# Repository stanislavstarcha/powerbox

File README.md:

# Install and run firmware

Add paths to your bash/zsh rc for convenience 

```shell
export POWERBOX_HOME=$HOME/powerbox
export LVGL_HOME=$HOME/lvgl_micropython
```

```shell
mkdir $POWERBOX_HOME
cd $POWERBOX_HOME
git clone https://github.com/stanislavstarcha/powerbox .
```

## Install LVGL micropython

```shell
mkdir $LVGL_HOME
cd $LVGL_HOME
git clone https://github.com/lvgl-micropython/lvgl_micropython .
```

### Copy fonts
```shell
cd $POWEBOX_HOME
cp ./resources/fonts/Roboto-Black.ttf $LVGL_HOME/lib/lvgl/scripts/built_in_font
cp ./resources/fonts/Roboto-Regular.ttf $LVGL_HOME/lib/lvgl/scripts/built_in_font
cp ./resources/fonts/Material-Sharp-28.ttf $LVGL_HOME/lib/lvgl/scripts/built_in_font

```

### Build fonts

Modify `$LVGL_HOME/lib/lvgl/scripts/built_in_font/generate_all.py` and add 

```python
print("\nGenerating 12 px Roboto Ukrainian")
os.system("lv_font_conv --no-compress --no-prefilter --bpp 2 --size 12 --font Roboto-Regular.ttf --format lvgl -o lv_font_roboto_12.c -r 0xB0,0x20-0x22,0x25,0x27-0x40,0x5B-0x5F,0x7B-0x7D,0xA0,0xA7,0xA9,0xAB,0xBB,0x2BC,0x404,0x406-0x407,0x410-0x429,0x42C,0x42E-0x449,0x44C,0x44E-0x44F,0x454,0x456-0x457,0x490-0x491,0x2011,0x2013,0x2019,0x201C,0x201E,0x2030,0x20AC,0x2116")

print("\nGenerating 24 px Glyphs")
os.system("lv_font_conv --no-compress --no-prefilter --bpp 2 --size 24 --font Material-Sharp-28.ttf --format lvgl -o lv_font_material_24.c -r 0xEAC3,0xEAC9,0xEAD0,0xEACF,0xE000,0xe1a7,0xe1a8,0xf156,0xE7EE,0xe5d3,0xe322,0xe87d")

print("\nGenerating 24 px Roboto")
os.system("lv_font_conv --no-compress --no-prefilter --bpp 2 --size 26 --font Roboto-Black.ttf --format lvgl -o lv_font_roboto_24.c -r 0x20,0x30-0x39,0x412,0x442")

print("\nGenerating 120 px Roboto")
os.system("lv_font_conv --no-compress --no-prefilter --bpp 2 --size 120 --font Roboto-Black.ttf --format lvgl -o lv_font_roboto_120.c --symbols 0123456789%")
```

and then build the fonts

```shell
cd $LVGL_HOME/lib/lvgl/scripts/built_in_font
python generate_all.py
```

### Modify headers

Open `$LVGL_HOME/lib/lvconf.h`

Set to 0 (disable) all `#define LV_FONT_MONTSERRAT_*`
and define custom fonts built earlier.

```
#define LV_FONT_MONTSERRAT_14 0
...

#define LV_FONT_CUSTOM_DECLARE LV_FONT_DECLARE(lv_font_roboto_12) LV_FONT_DECLARE(lv_font_roboto_24) LV_FONT_DECLARE(lv_font_roboto_120) LV_FONT_DECLARE(lv_font_material_24)

#define LV_FONT_DEFAULT &lv_font_roboto_12
```

## Build firmware

```shell
cd $LVGL_HOME
python make.py esp32 BOARD=ESP32_GENERIC_S3 DISPLAY=ILI9488 \
FROZEN_MANIFEST=$POWERBOX_HOME/manifest.py BOARD_VARIANT=SPIRAM_OCT \
--flash-size=16 \ 
--ota
```

### Flash firmware

Connect ESP32-S3 to USB and find the port `ls /dev/tty*`

A typical serial port should look like this 
- `/dev/tty.usbmodem11101`
- `/dev/cu.usbserial-0001`
- `/dev/tty.usbmodem1234561`

Note: On MacOS you may need a CH34xVCPDriver that would create a new port like
`/dev/tty.wchusbserial59710258441`

```shell
cd $LVGL_HOME

python -m esptool --chip esp32s3 -p /dev/tty.wchusbserial59710258441 \
-b 460800 --before default_reset --after hard_reset write_flash \
--flash_mode dio --flash_size 16MB --flash_freq 80m --erase-all \
0x0 /Users/stasstarcha/workspace/lvgl_micropython/build/lvgl_micropy_ESP32_GENERIC_S3-SPIRAM_OCT-16.bin
```

### Build release

Specify the version and run the command to produce bin and json files that
should be attached to a release on GitHub.

```shell
cd $POWEBOX_HOME
python scripts/release.py --version=0.10.0 \
--path=$LVGL_HOME/lib/micropython/ports/esp32/build-ESP32_GENERIC_S3-SPIRAM_OCT/micropython.bin \
--output=../build
 ```

## Development mode

During development, it's easier to update files one by one.

```shell
python initialize.py \
--baud_rate 115200 \
--port /dev/cu.usbserial-0001
```

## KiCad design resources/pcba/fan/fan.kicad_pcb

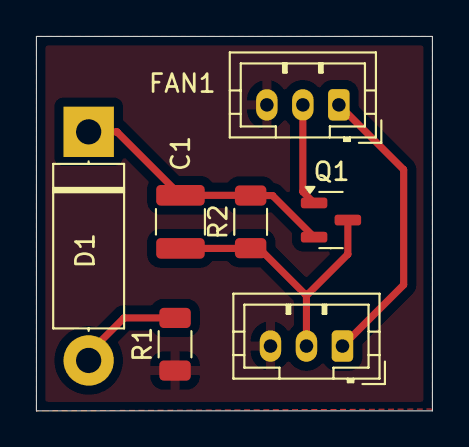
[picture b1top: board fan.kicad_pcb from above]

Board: 2 copper layers, 22.0 x 20.8 mm, 7 parts (0 on the bottom side), 6 nets.

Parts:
C1: 10u; C_1210_3225Metric
D1: D_Zener; D_5W_P12.70mm_Horizontal
FAN1: Conn_01x03_Socket; JST_PH_B3B-PH-K_1x03_P2.00mm_Vertical
INV1: Conn_01x03_Socket; JST_PH_B3B-PH-K_1x03_P2.00mm_Vertical
Q1: PMOS; SOT-23
R1: 1k; R_1206_3216Metric
R2: 10k; R_1206_3216Metric

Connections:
/FAN: FAN1.2 (+), Q1.1 (D)
/TACHOMETER: FAN1.1 (TACH), INV1.1 (TACH)
GND: FAN1.3 (GND), INV1.3 (GND), R1.1
unnamed: D1.2 (A), R1.2
unnamed: C1.1, D1.1 (K), Q1.2 (G), R2.2
unnamed: C1.2, INV1.2 (+), Q1.3 (S), R2.1

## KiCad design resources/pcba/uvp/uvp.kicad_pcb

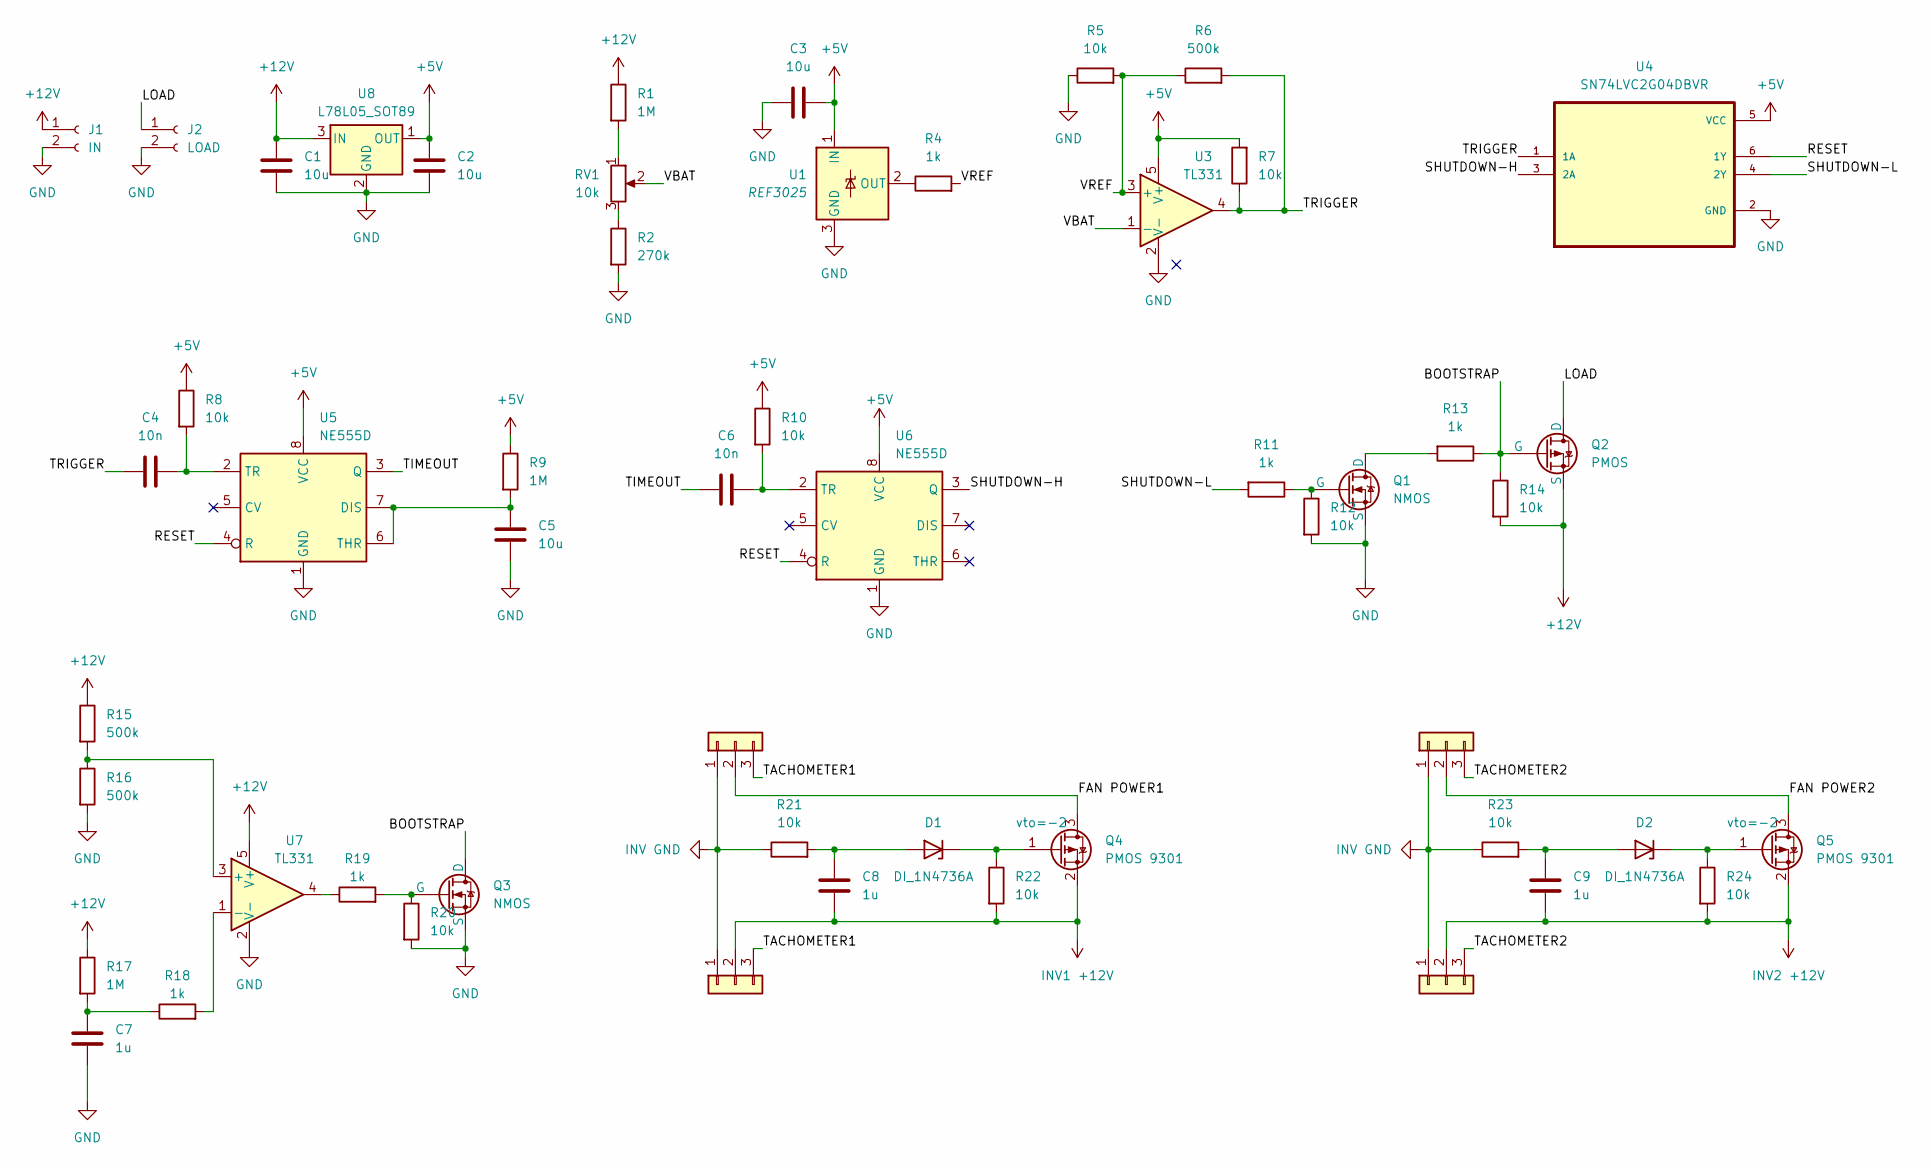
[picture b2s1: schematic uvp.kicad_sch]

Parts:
C1, C2, C3: 10u; C_0805_2012Metric_Pad1.18x1.45mm_HandSolder
C4, C6: 10n; C_0805_2012Metric_Pad1.18x1.45mm_HandSolder
C5: 10u; C_1210_3225Metric_Pad1.33x2.70mm_HandSolder
C7: 1u; C_0805_2012Metric_Pad1.18x1.45mm_HandSolder
C8, C9: 1u; C_1210_3225Metric
D1, D2: D_Zener; D_5W_P12.70mm_Horizontal
IN1: FAN1; JST_PH_S3B-PH-K_1x03_P2.00mm_Horizontal
IN2: INV FAN1; JST_PH_S3B-PH-K_1x03_P2.00mm_Horizontal
IN3: FAN2; JST_PH_S3B-PH-K_1x03_P2.00mm_Horizontal
IN4: INV FAN2; JST_PH_S3B-PH-K_1x03_P2.00mm_Horizontal
J1: IN; JST_XH_S2B-XH-A_1x02_P2.50mm_Horizontal
J2: LOAD; JST_XH_S2B-XH-A_1x02_P2.50mm_Horizontal
Q1, Q3: NMOS; SOT-23
Q2: PMOS; TO-252-2
Q4, Q5: PMOS 9301; SOT-23
R1, R9, R17: 1M; R_0805_2012Metric_Pad1.20x1.40mm_HandSolder
R2: 270k; R_0805_2012Metric_Pad1.20x1.40mm_HandSolder
R4, R11, R13, R18, R19: 1k; R_0805_2012Metric_Pad1.20x1.40mm_HandSolder
R5, R7, R8, R10, R12, R14, R20: 10k; R_0805_2012Metric_Pad1.20x1.40mm_HandSolder
R6, R15, R16: 500k; R_0805_2012Metric_Pad1.20x1.40mm_HandSolder
R21, R22, R23, R24: 10k; R_1206_3216Metric
RV1: 10k; Potentiometer_Runtron_RM-063_Horizontal
U1: REF3025; SOT-23
U3, U7: TL331; SOT-23-5
U4: SN74LVC2G04DBVR; SOT95P280X145-6N
U5, U6: NE555D; SOIC-8_3.9x4.9mm_P1.27mm
U8: L78L05_SOT89; SOT-89-3

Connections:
+5V: C2.2, C3.1, R7.2, R8.1, R9.1, R10.1, U1.1 (IN), U3.5 (V+), U4.5 (VCC), U5.8 (VCC), U6.8 (VCC), U8.1 (OUT)
+12V: C1.2, J1.1, Q2.3 (S), R1.1, R14.2, R15.1, R17.1, U7.5 (V+), U8.3 (IN)
/BOOTSTRAP: Q2.2 (G), Q3.1 (D), R13.1, R14.1
/FAN POWER1: IN1.2, Q4.3 (D)
/FAN POWER2: IN3.2, Q5.3 (D)
/LOAD: J2.1, Q2.1 (D)
/RESET: U4.6 (1Y), U5.4 (R), U6.4 (R)
/SHUTDOWN-H: U4.3 (2A), U6.3 (Q)
/SHUTDOWN-L: R11.2, U4.4 (2Y)
/TACHOMETER1: IN1.3, IN2.3
/TACHOMETER2: IN3.3, IN4.3
/TIMEOUT: C6.1, U5.3 (Q)
/TRIGGER: C4.1, R6.2, R7.1, U3.4, U4.1 (1A)
/VBAT: RV1.2, U3.1 (-)
/VREF: R4.2, R5.2, R6.1, U3.3 (+)
GND: C1.1, C2.1, C3.2, C5.1, C7.2, J1.2, J2.2, Q1.3 (S), Q3.3 (S), R2.2, R5.1, R12.2, R16.2, R20.2, U1.3 (GND), U3.2 (V-), U4.2 (GND), U5.1 (GND), U6.1 (GND), U7.2 (V-), U8.2 (GND)
INV1 +12V: C8.2, IN2.2, Q4.2 (S), R22.2
INV2 +12V: C9.2, IN4.2, Q5.2 (S), R24.2
INV GND: IN1.1, IN2.1, IN3.1, IN4.1, R21.1, R23.1
unnamed: C7.1, R17.2, R18.1
unnamed: C8.1, D1.2 (A), R21.2
unnamed: D1.1 (K), Q4.1 (G), R22.1
unnamed: C9.1, D2.2 (A), R23.2
unnamed: D2.1 (K), Q5.1 (G), R24.1
unnamed: Q1.1 (D), R13.2
unnamed: Q1.2 (G), R11.1, R12.1
unnamed: Q3.2 (G), R19.2, R20.1
unnamed: R1.2, RV1.1
unnamed: R2.1, RV1.3
unnamed: R19.1, U7.4
unnamed: R4.1, U1.2 (OUT)
unnamed: C5.2, R9.2, U5.6 (THR), U5.7 (DIS)
unnamed: C4.2, R8.2, U5.2 (TR)
unnamed: C6.2, R10.2, U6.2 (TR)
unnamed: R15.2, R16.1, U7.3 (+)
unnamed: R18.2, U7.1 (-)

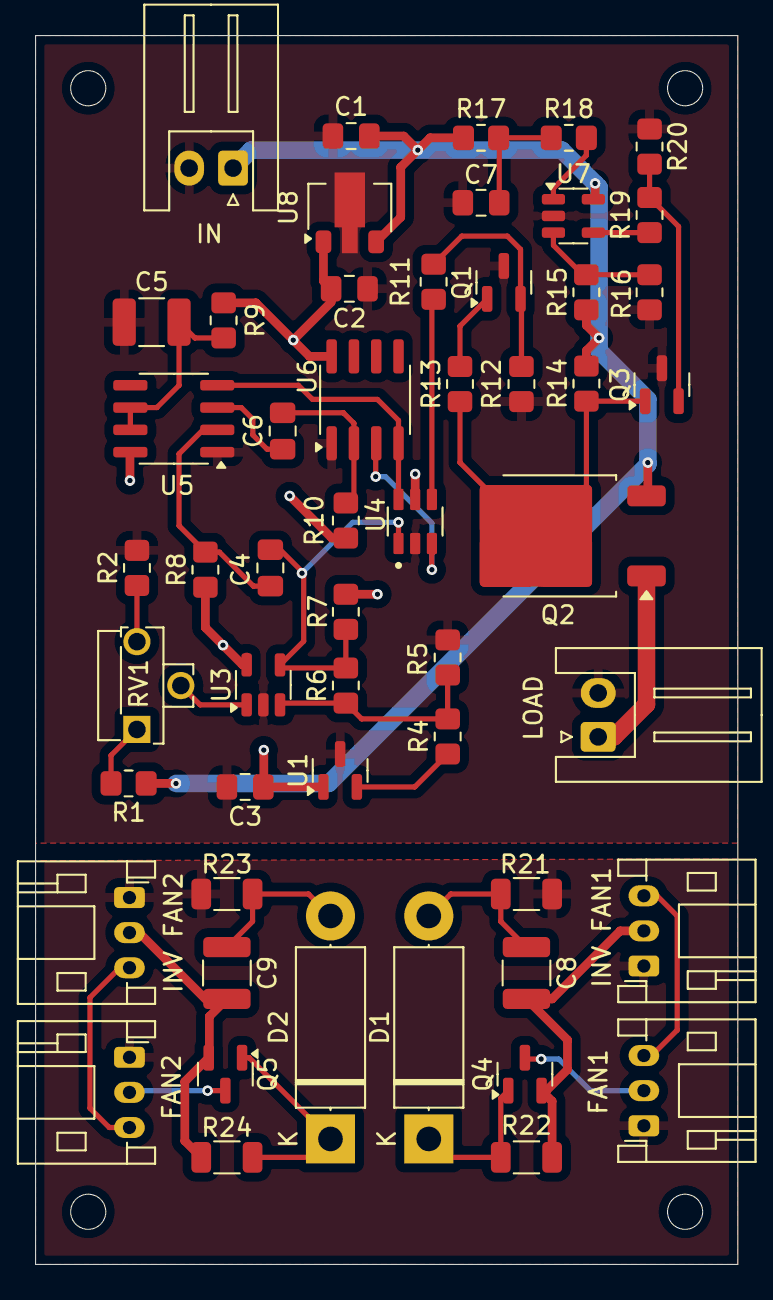
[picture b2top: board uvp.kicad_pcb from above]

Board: 2 copper layers, 40.0 x 70.0 mm, 53 parts (0 on the bottom side), 36 nets.

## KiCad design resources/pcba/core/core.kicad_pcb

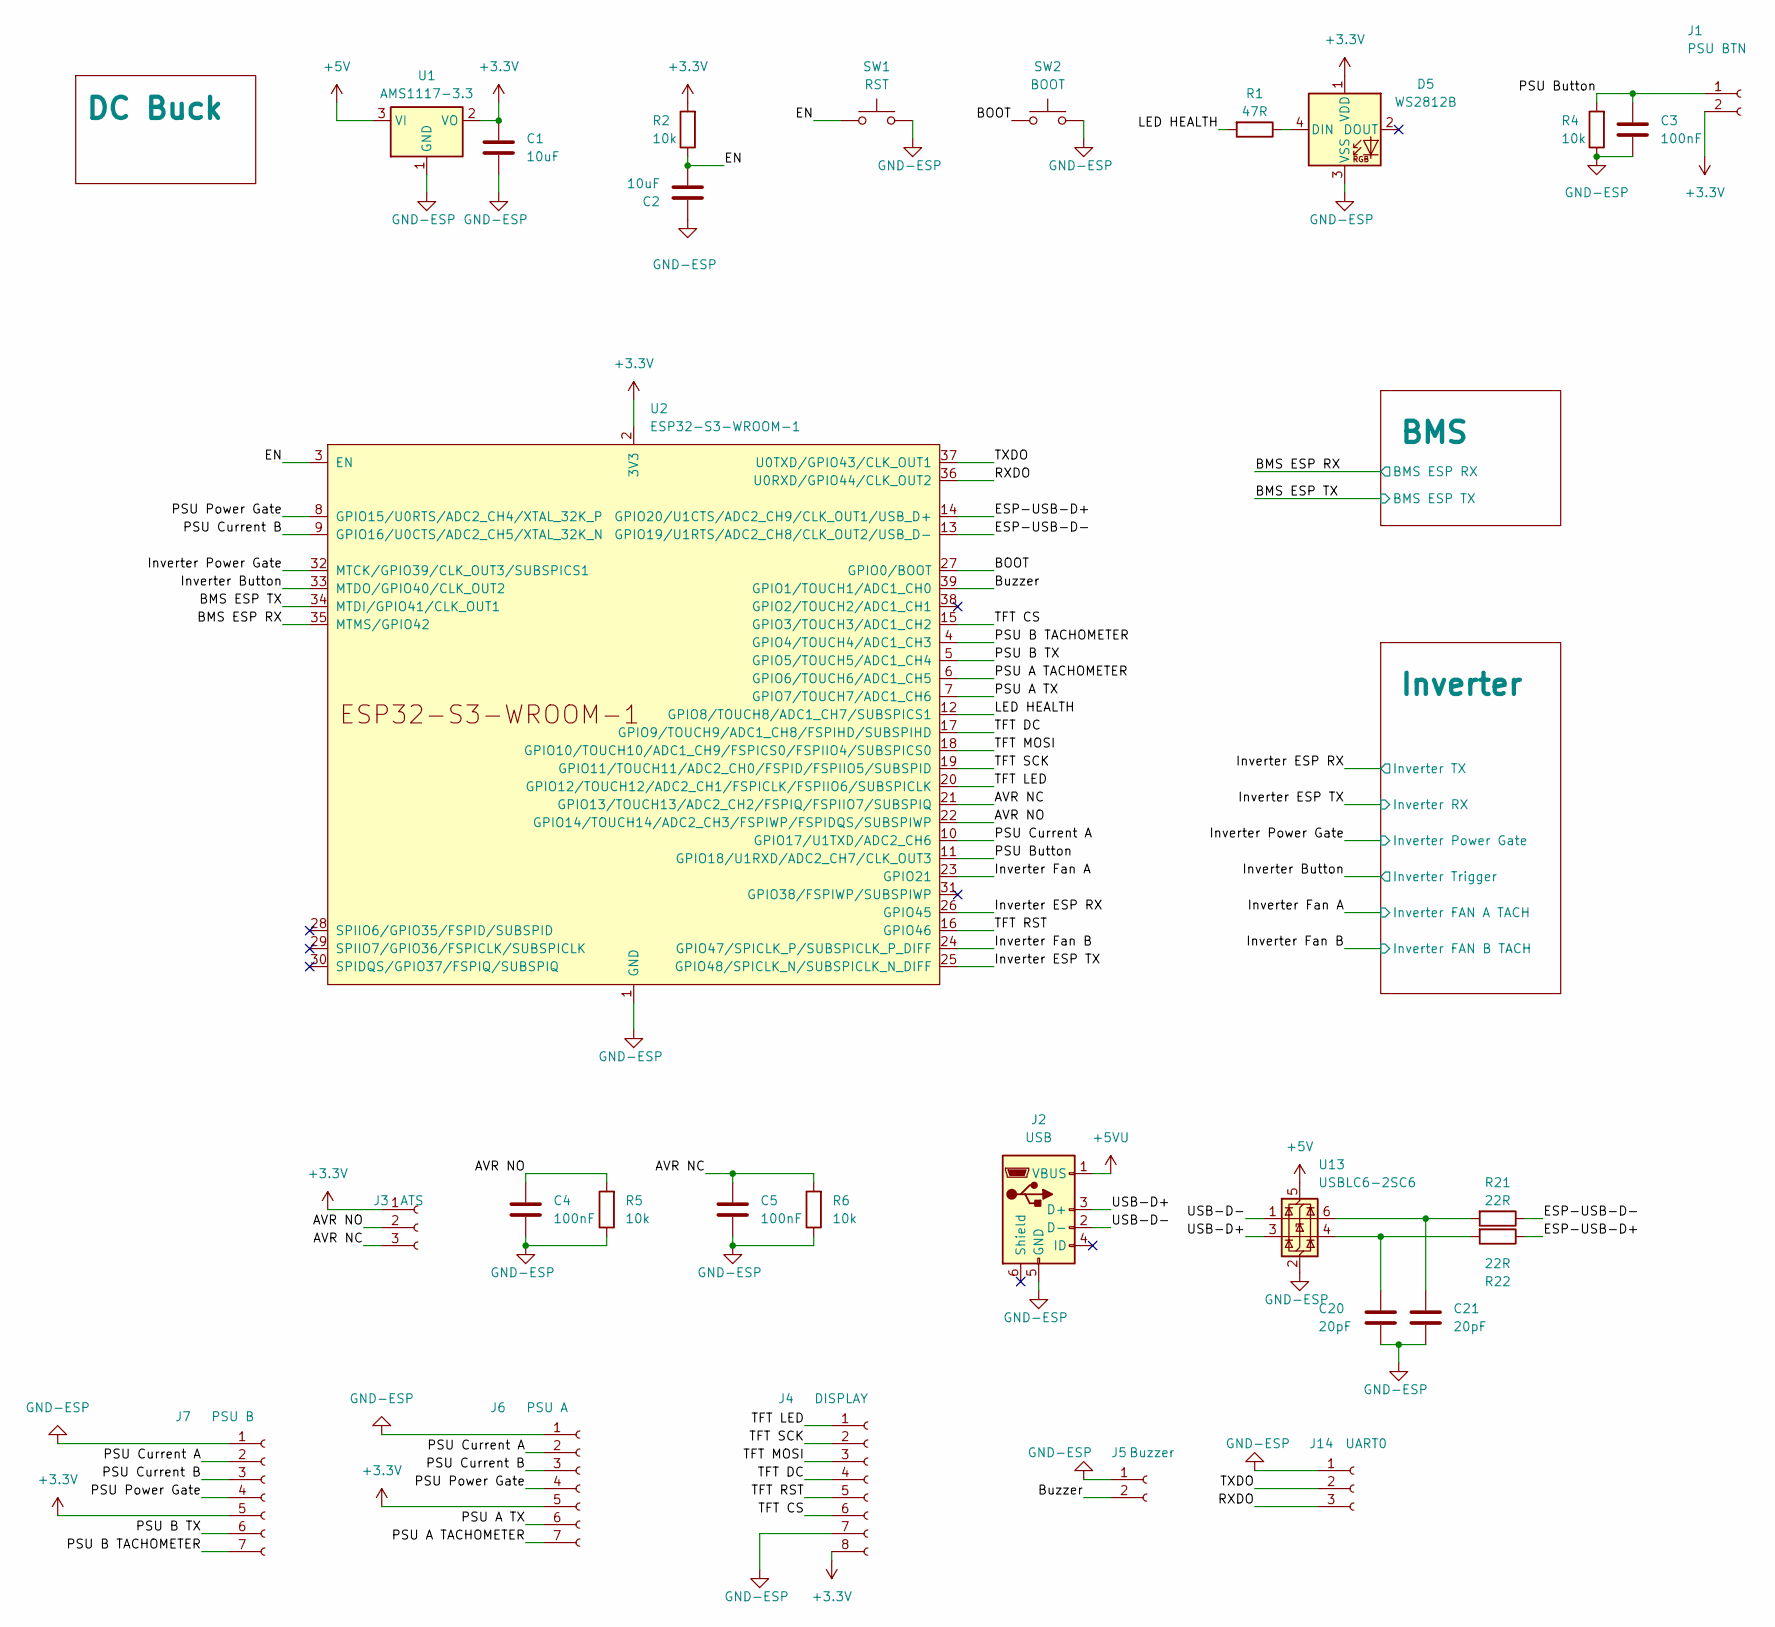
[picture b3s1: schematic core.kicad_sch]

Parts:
C1, C2: 10uF; C_1206_3216Metric
C3, C4, C5: 100nF; C_1206_3216Metric
C20, C21: 20pF; C_0805_2012Metric
D5: WS2812B; LED_WS2812B_PLCC4_5.0x5.0mm_P3.2mm
J1: PSU BTN; JST_PH_B2B-PH-K_1x02_P2.00mm_Vertical
J2: USB; USB_Micro-B_Molex-105017-0001
J3: ATS; JST_PH_B3B-PH-K_1x03_P2.00mm_Vertical
J4: DISPLAY; JST_PH_B8B-PH-K_1x08_P2.00mm_Vertical
J5: Buzzer; JST_PH_B2B-PH-K_1x02_P2.00mm_Vertical
J6: PSU A; JST_PH_B7B-PH-K_1x07_P2.00mm_Vertical
J7: PSU B; JST_PH_B7B-PH-K_1x07_P2.00mm_Vertical
J14: UART0; JST_PH_B3B-PH-K_1x03_P2.00mm_Vertical
R1: 47R; R_0805_2012Metric
R2, R4, R5, R6: 10k; R_1206_3216Metric
R21, R22: 22R; R_0805_2012Metric
SW1: RST; SW_Push_SPST_NO_Alps_SKRK
SW2: BOOT; SW_Push_SPST_NO_Alps_SKRK
U1: AMS1117-3.3; SOT-223-3_TabPin2
U2: ESP32-S3-WROOM-1
U13: USBLC6-2SC6; SOT-23-6

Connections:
+3.3V: C1.1, D5.1 (VDD), J1.2, J3.1, J4.8, J6.5, J7.5, R2.2, U1.2 (VO), U2.2 (3V3); also elsewhere on the board
+5V: U1.3 (VI), U13.5 (VBUS); also elsewhere on the board
+5VU: J2.1 (VBUS); also elsewhere on the board
/AVR NC: C5.1, J3.3, R6.2, U2.21 (GPIO13/TOUCH13/ADC2_CH2/FSPIQ/FSPIIO7/S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)
/AVR NO: C4.1, J3.2, R5.2, U2.22 (GPIO14/TOUCH14/ADC2_CH3/FSPIWP/FSPIDQS/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)
/BMS ESP RX: U2.35 (MTMS/GPIO42); also elsewhere on the board
/BMS ESP TX: U2.34 (MTDI/GPIO41/CLK_OUT1); also elsewhere on the board
/BOOT: SW2.1, U2.27 (GPIO0/BOOT)
/Buzzer: J5.2, U2.39 (GPIO1/TOUCH1/ADC1_CH0)
/EN: C2.2, R2.1, SW1.1, U2.3 (EN)
/ESP-USB-D+: R22.1, U2.14 (GPIO20/U1CTS/ADC2_CH9/CLK_OUT1/USB_D+)
/ESP-USB-D-: R21.1, U2.13 (GPIO19/U1RTS/ADC2_CH8/CLK_OUT2/USB_D-)
/Inverter Button: U2.33 (MTDO/GPIO40/CLK_OUT2); also elsewhere on the board
/Inverter ESP RX: U2.26 (GPIO45); also elsewhere on the board
/Inverter ESP TX: U2.25 (GPIO48/SPICLK_N/SUBSPICLK_N_DIFF); also elsewhere on the board
/Inverter Fan A: U2.23 (GPIO21); also elsewhere on the board
/Inverter Fan B: U2.24 (GPIO47/SPICLK_P/SUBSPICLK_P_DIFF); also elsewhere on the board
/Inverter Power Gate: U2.32 (MTCK/GPIO39/CLK_OUT3/SUBSPICS1); also elsewhere on the board
/LED HEALTH: R1.2, U2.12 (GPIO8/TOUCH8/ADC1_CH7/SUBSPICS1)
/PSU A TACHOMETER: J6.7, U2.6 (GPIO6/TOUCH6/ADC1_CH5)
/PSU A TX: J6.6, U2.7 (GPIO7/TOUCH7/ADC1_CH6)
/PSU B TACHOMETER: J7.7, U2.4 (GPIO4/TOUCH4/ADC1_CH3)
/PSU B TX: J7.6, U2.5 (GPIO5/TOUCH5/ADC1_CH4)
/PSU Button: C3.1, J1.1, R4.2, U2.11 (GPIO18/U1RXD/ADC2_CH7/CLK_OUT3)
/PSU Current A: J6.2, J7.2, U2.10 (GPIO17/U1TXD/ADC2_CH6)
/PSU Current B: J6.3, J7.3, U2.9 (GPIO16/U0CTS/ADC2_CH5/XTAL_32K_N)
/PSU Power Gate: J6.4, J7.4, U2.8 (GPIO15/U0RTS/ADC2_CH4/XTAL_32K_P)
/RXDO: J14.3, U2.36 (U0RXD/GPIO44/CLK_OUT2)
/TFT CS: J4.6, U2.15 (GPIO3/TOUCH3/ADC1_CH2)
/TFT DC: J4.4, U2.17 (GPIO9/TOUCH9/ADC1_CH8/FSPIHD/SUBSPIHD)
/TFT LED: J4.1, U2.20 (GPIO12/TOUCH12/ADC2_CH1/FSPICLK/FSPIIO6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)
/TFT MOSI: J4.3, U2.18 (GPIO10/TOUCH10/ADC1_CH9/FSPICS0/FSPIIO4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)
/TFT RST: J4.5, U2.16 (GPIO46)
/TFT SCK: J4.2, U2.19 (GPIO11/TOUCH11/ADC2_CH0/FSPID/FSPIIO5/S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)
/TXDO: J14.2, U2.37 (U0TXD/GPIO43/CLK_OUT1)
/USB-D+: J2.3 (D+), U13.3 (I/O2)
/USB-D-: J2.2 (D-), U13.1 (I/O1)
GND-ESP: C1.2, C2.1, C3.2, C4.2, C5.2, C20.2, C21.2, D5.3 (VSS), J2.5 (GND), J4.7, J5.1, J6.1, J7.1, J14.1, R4.1, R5.1, R6.1, SW1.2, SW2.2, U1.1 (GND), U2.1 (GND), U2.40 (GND), U2.41 (GND), U13.2 (GND); also elsewhere on the board
unnamed: C20.1, R22.2, U13.4 (I/O2)
unnamed: C21.1, R21.2, U13.6 (I/O1)
unnamed: D5.4 (DIN), R1.1

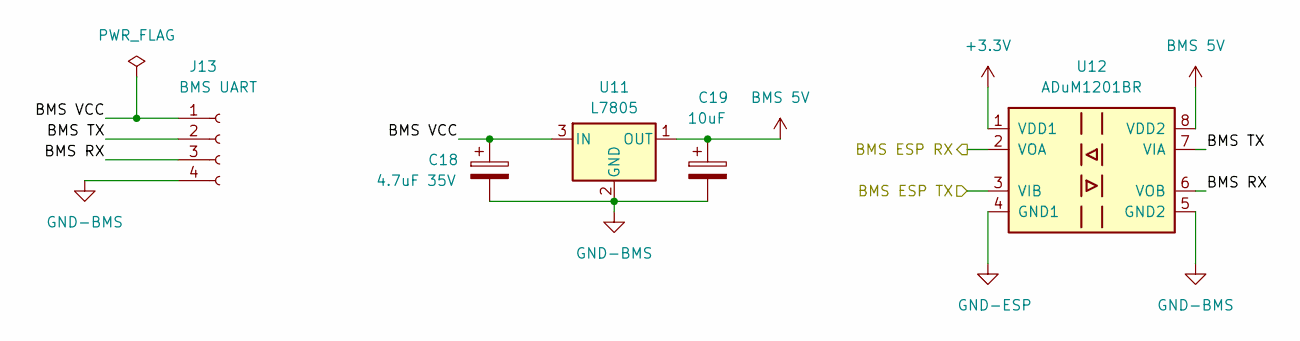
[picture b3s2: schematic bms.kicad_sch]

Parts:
C18: 4.7uF 35V; CP_EIA-6032-28_Kemet-C
C19: 10uF; C_1206_3216Metric
J13: BMS UART; JST_PH_B4B-PH-K_1x04_P2.00mm_Vertical
U11: L7805; SOT-89-3
U12: ADuM1201BR; SOIC-8_3.9x4.9mm_P1.27mm

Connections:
+3.3V: U12.1 (VDD1); also elsewhere on the board
/BMS ESP RX: U12.2 (VOA); also elsewhere on the board
/BMS ESP TX: U12.3 (VIB); also elsewhere on the board
/BMS/BMS RX: J13.3, U12.6 (VOB)
/BMS/BMS TX: J13.2, U12.7 (VIA)
/BMS/BMS VCC: C18.1, J13.1, U11.3 (IN)
BMS 5V: C19.1, U11.1 (OUT), U12.8 (VDD2)
GND-BMS: C18.2, C19.2, J13.4, U11.2 (GND), U12.5 (GND2)
GND-ESP: U12.4 (GND1); also elsewhere on the board

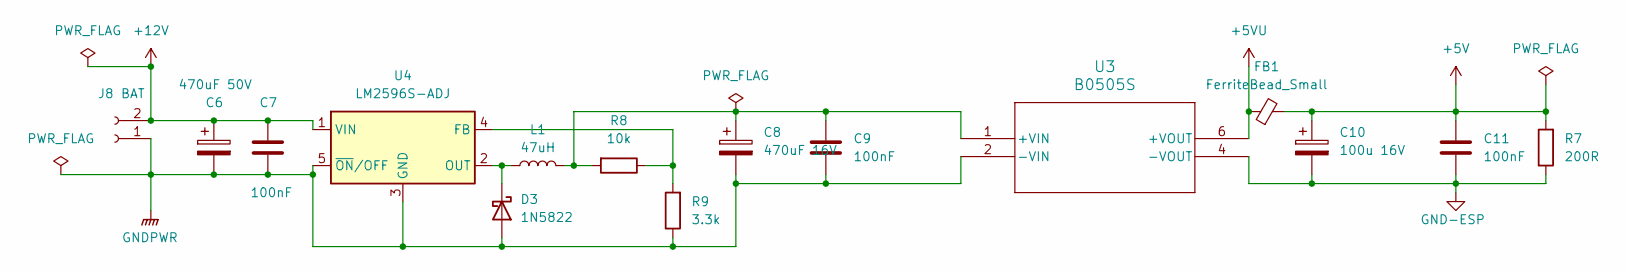
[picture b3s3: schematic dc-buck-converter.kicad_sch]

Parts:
C6: 470uF 50V; CP_Radial_D10.0mm_P3.80mm
C7, C9: 100nF; C_1206_3216Metric
C8: 470uF 16V; CP_Radial_D8.0mm_P3.50mm
C10: 100u 16V; CP_EIA-7343-31_Kemet-D
C11: 100nF; C_0805_2012Metric
D3: 1N5822; D_SMA
FB1: FerriteBead_Small; L_1206_3216Metric
J8: BAT; JST_XH_B2B-XH-A_1x02_P2.50mm_Vertical
L1: 47uH; L_12x12mm_H6mm
R7: 200R; R_1206_3216Metric
R8: 10k; R_1206_3216Metric
R9: 3.3k; R_1206_3216Metric
U3: B0505S
U4: LM2596S-ADJ; TO-263-5_TabPin3

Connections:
+5V: C10.1, C11.1, FB1.2, R7.2; also elsewhere on the board
+5VU: FB1.1, U3.6 (+VOUT); also elsewhere on the board
+12V: C6.1, C7.1, J8.2, U4.1 (VIN)
GND-ESP: C10.2, C11.2, R7.1, U3.4 (-VOUT); also elsewhere on the board
GNDPWR: C6.2, C7.2, C8.2, C9.2, D3.2 (A), J8.1, R9.1, U3.2 (-VIN), U4.3 (GND), U4.5 (~ON/OFF)
unnamed: D3.1 (K), L1.1, U4.2 (OUT)
unnamed: C8.1, C9.1, L1.2, R8.2, U3.1 (+VIN)
unnamed: R8.1, R9.2, U4.4 (FB)

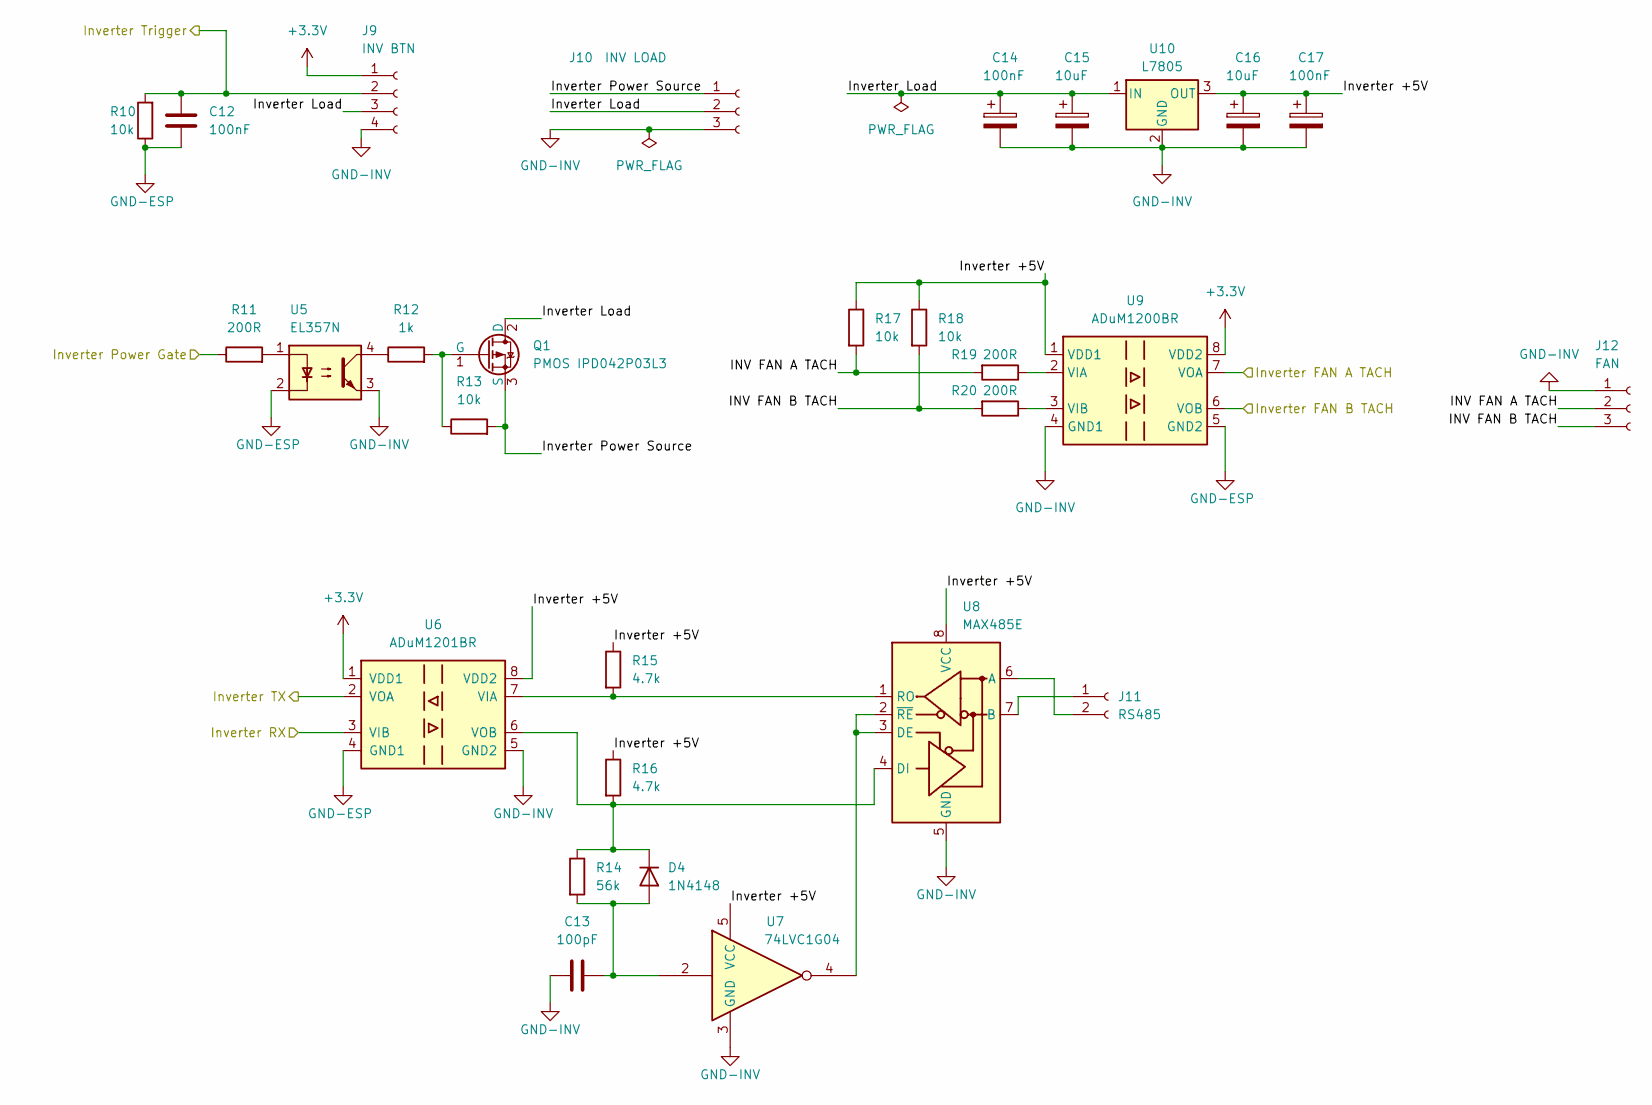
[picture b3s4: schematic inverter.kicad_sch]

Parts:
C12, C14, C17: 100nF; C_1206_3216Metric
C13: 100pF; C_1206_3216Metric
C15, C16: 10uF; C_1206_3216Metric
D4: 1N4148; D_SOD-123
J9: INV BTN; JST_PH_B4B-PH-K_1x04_P2.00mm_Vertical
J10: INV LOAD; JST_PH_B3B-PH-K_1x03_P2.00mm_Vertical
J11: RS485; JST_XH_B2B-XH-A_1x02_P2.50mm_Vertical
J12: FAN; JST_PH_B3B-PH-K_1x03_P2.00mm_Vertical
Q1: PMOS IPD042P03L3; TO-252-2
R10, R13, R17, R18: 10k; R_1206_3216Metric
R11, R19, R20: 200R; R_1206_3216Metric
R12: 1k; R_1206_3216Metric
R14: 56k; R_1206_3216Metric
R15, R16: 4.7k; R_1206_3216Metric
U5: EL357N; SO-4_4.4x4.3mm_P2.54mm
U6: ADuM1201BR; SOIC-8_3.9x4.9mm_P1.27mm
U7: 74LVC1G04; SOT-23-5
U8: MAX485E; SOIC-8_3.9x4.9mm_P1.27mm
U9: ADuM1200BR; SOIC-8_3.9x4.9mm_P1.27mm
U10: L7805; TO-252-2

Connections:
+3.3V: J9.1, U6.1 (VDD1), U9.8 (VDD2); also elsewhere on the board
/Inverter Button: C12.1, J9.2, R10.2; also elsewhere on the board
/Inverter ESP RX: U6.2 (VOA); also elsewhere on the board
/Inverter ESP TX: U6.3 (VIB); also elsewhere on the board
/Inverter Fan A: U9.7 (VOA); also elsewhere on the board
/Inverter Fan B: U9.6 (VOB); also elsewhere on the board
/Inverter Power Gate: R11.1; also elsewhere on the board
/Inverter/INV FAN A TACH: J12.2, R17.2, R19.2
/Inverter/INV FAN B TACH: J12.3, R18.2, R20.2
/Inverter/Inverter +5V: C16.1, C17.1, R15.1, R16.1, R17.1, R18.1, U6.8 (VDD2), U7.5 (VCC), U8.8 (VCC), U9.1 (VDD1), U10.3 (OUT)
/Inverter/Inverter Load: C14.1, C15.1, J9.3, J10.2, Q1.2 (D), U10.1 (IN)
/Inverter/Inverter Power Source: J10.1, Q1.3 (S), R13.2
GND-ESP: C12.2, R10.1, U5.2, U6.4 (GND1), U9.5 (GND2); also elsewhere on the board
GND-INV: C13.1, C14.2, C15.2, C16.2, C17.2, J9.4, J10.3, J12.1, U5.3, U6.5 (GND2), U7.3 (GND), U8.5 (GND), U9.4 (GND1), U10.2 (GND)
unnamed: C13.2, D4.2 (A), R14.2, U7.2
unnamed: D4.1 (K), R14.1, R16.2, U6.6 (VOB), U8.4 (DI)
unnamed: J11.1, U8.7 (B)
unnamed: J11.2, U8.6 (A)
unnamed: Q1.1 (G), R12.2, R13.1
unnamed: R11.2, U5.1
unnamed: R12.1, U5.4
unnamed: R15.2, U6.7 (VIA), U8.1 (RO)
unnamed: U7.4, U8.2 (~RE), U8.3 (DE)
unnamed: R19.1, U9.2 (VIA)
unnamed: R20.1, U9.3 (VIB)

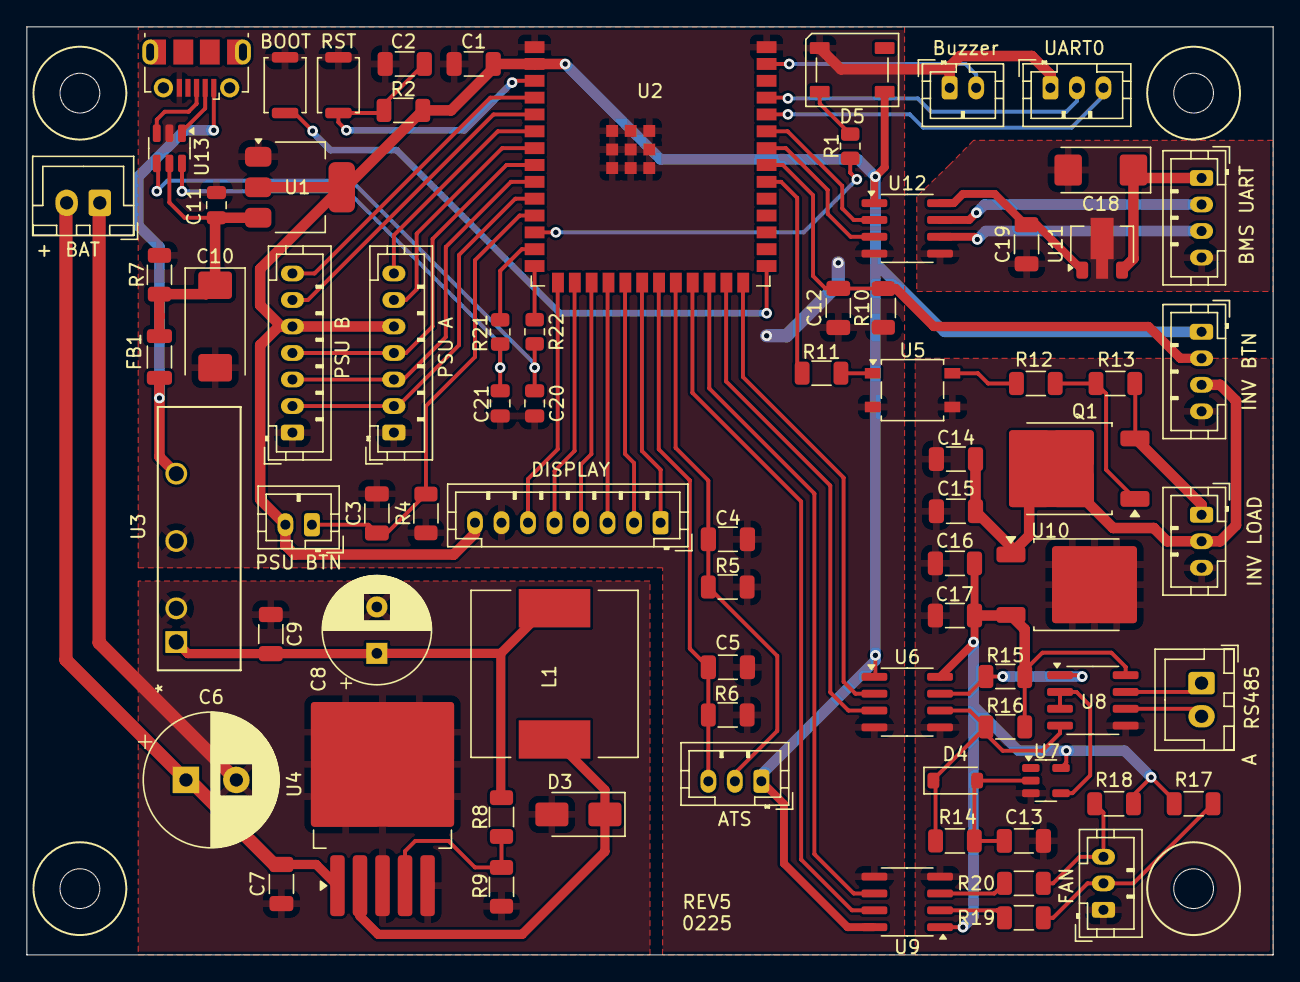
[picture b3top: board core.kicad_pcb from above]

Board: 2 copper layers, 94.0 x 70.0 mm, 77 parts (0 on the bottom side), 68 nets.

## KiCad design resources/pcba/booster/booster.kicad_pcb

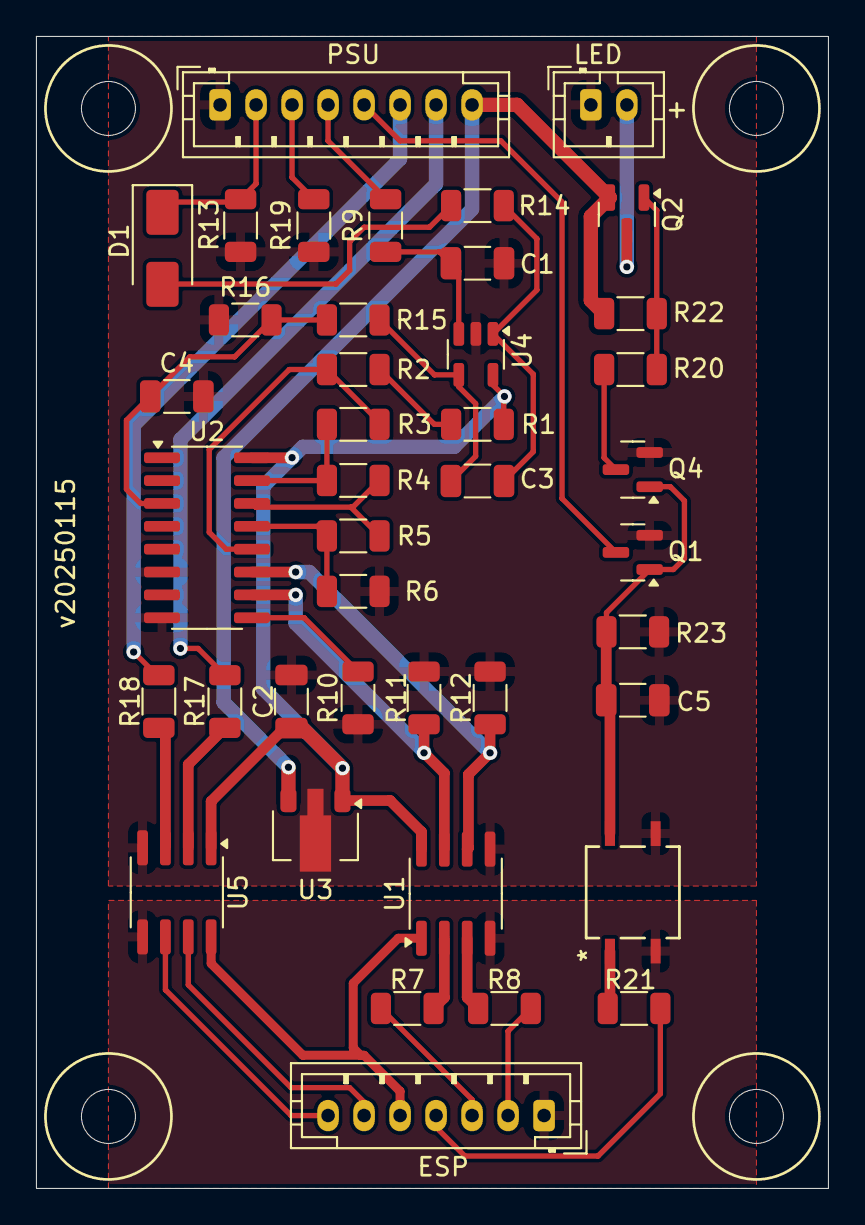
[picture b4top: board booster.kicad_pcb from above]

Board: 2 copper layers, 44.0 x 64.0 mm, 41 parts (0 on the bottom side), 38 nets.

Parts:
C1, C3, C4: 100nF; C_1206_3216Metric
C2: 1uF; C_1206_3216Metric
C5: 200pF; C_1206_3216Metric
D1: 1N4007; D_SMA
J1: LED; JST_PH_B2B-PH-K_1x02_P2.00mm_Vertical
J2: PSU; JST_PH_B8B-PH-K_1x08_P2.00mm_Vertical
J3: ESP; JST_PH_B7B-PH-K_1x07_P2.00mm_Vertical
Q1, Q4: IRLML0030; SOT-23
Q2: PMOS 9301; SOT-23
Q3: VOM1271T
R1: 3.9k; R_1206_3216Metric
R2: 390R; R_1206_3216Metric
R3, R4, R5, R6, R9, R14, R15: 1k; R_1206_3216Metric
R7, R8, R17, R18, R21: 200R; R_1206_3216Metric
R10, R11, R12, R22: 10k; R_1206_3216Metric
R13: 15k; R_1206_3216Metric
R16: 100k; R_1206_3216Metric
R19: 75k; R_1206_3216Metric
R20: 50R; R_1206_3216Metric
R23: 1M; R_1206_3216Metric
U1, U5: ADuM1200BR; SOIC-8_3.9x4.9mm_P1.27mm
U2: CD4051B; SOP-16_3.9x9.9mm_P1.27mm
U3: L78L05_SOT89; SOT-89-3
U4: MCP6001-OT; SOT-23-5

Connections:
+3.3V: J3.5, U1.1 (VDD1), U5.8 (VDD2)
/PSU A TACHOMETER: J3.7, U5.6 (VOB)
/PSU A TX: J3.6, U5.7 (VOA)
/PSU Current A: J3.2, R8.2
/PSU Current B: J3.3, R7.2
/PSU Power Gate: J3.4, R21.2
/PSU/MUX CUR A: R12.2, U1.6 (VOB), U2.11 (A)
/PSU/MUX CUR B: R11.2, U1.7 (VOA), U2.10 (B)
/PSU/PSU Button LED: J1.2, Q2.3 (D)
/PSU/PSU ON: J2.5, Q1.3 (D)
/PSU/PSU SIG1: D1.1 (K), J2.2, R13.1
/PSU/PSU SIG2: J2.3, R19.2
/PSU/PSU SIG3: J2.4, R9.2
/PSU/PSU TACHOMETER: J2.6, R18.2
/PSU/PSU TX: J2.7, R17.2
GND-ESP: J3.1, Q3.2, U1.4 (GND1), U5.5 (GND2)
GND-PSU: C1.2, C2.2, C4.2, C5.2, J1.1, J2.1, Q1.2 (S), Q3.3, Q4.2 (S), R6.1, R10.1, R11.1, R12.1, R13.2, R16.1, R19.1, R23.1, U1.5 (GND2), U2.6 (INH), U2.8 (VSS), U3.2 (GND), U4.2 (V-), U5.4 (GND1)
unnamed: C3.2, R14.1, U4.1
unnamed: D1.2 (A), R14.2
unnamed: C5.1, Q1.1 (G), Q3.4, Q4.1 (G), R23.2
unnamed: Q2.1 (G), R20.2, R22.1
unnamed: Q3.1, R21.1
unnamed: Q4.3 (D), R20.1
unnamed: R1.1, R2.2
unnamed: R7.1, U1.2 (VIA)
unnamed: R8.1, U1.3 (VIB)
unnamed: R10.2, U2.9 (C)
unnamed: R5.1, R6.2, U2.13 (X0)
unnamed: R4.1, R5.2, U2.14 (X1)
unnamed: R3.1, R4.2, U2.15 (X2)
unnamed: R2.1, R3.2, U2.12 (X3)
unnamed: C4.1, R15.1, R16.2, U2.3 (X)
unnamed: C1.1, R9.1, U4.3 (+)
unnamed: C3.1, R15.2, U4.4 (-)
unnamed: R17.1, U5.2 (VIA)
unnamed: R18.1, U5.3 (VIB)
PSU +5V: C2.1, R1.2, U1.8 (VDD2), U2.16 (VDD), U3.1 (OUT), U4.5 (V+), U5.1 (VDD1)
PSU +12V: J2.8, Q2.2 (S), R22.2, U3.3 (IN)

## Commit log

2024-11-28 clean up
2024-11-29 basic i18n
2024-11-30 add ats store
2024-12-01 refactor config
2024-12-01 refactor mobile app
2024-12-02 use local storage for preferences
2024-12-08 minor adjustments
2025-01-15 support psu tachometer
2025-01-25 basic lvgl support
2025-01-25 fix font headers
2025-01-26 display state handler
2025-02-09 use dynamic uart
2025-02-12 add sleep screen
2025-02-13 add resources
2025-02-13 fix action reference
2025-03-03 various fixes
2025-03-03 add core pcba
2025-03-09 use hardware timers in buttons
2025-03-09 refactor display screens
2025-03-09 ignore kicad lock file
2025-03-09 add booster circuit
2025-03-09 update booster kicad lib
2025-03-10 fix ble communication
2025-03-12 update ble protocol
2025-03-13 adjust mobile app colors
2025-03-14 add prints
2025-03-16 basic ota support
2025-03-17 i18n for ota
2025-03-17 add scripts
2025-03-17 move initilize.py to scripts
2025-03-17 remove lock files
2025-03-17 move version to a separate file
2025-04-02 support logs over ble
2025-04-08 measure inverter fans properly
2025-04-08 add docstrings
2025-04-09 optimize imports
2025-04-09 minor tweaks
2025-04-12 various fixes and docstrings
2025-05-18 add fan circuit
2025-10-28 update display frequency
2025-10-28 add uvp and fan pcb
2025-10-28 remove artifacts
2025-10-28 add missing fan pcb components
2025-10-28 add capacitor for android
2025-10-28 fix release script
2025-10-28 reduce display frequency
2025-10-28 show patch version
2025-12-17 current mode and self consumption
2025-12-17 current mode version
2025-12-17 fix button bugs
2025-12-18 dynamically reduce psu current
2025-12-18 min charge current
2025-12-18 fix packing utils
2025-12-18 increase turn off voltage
